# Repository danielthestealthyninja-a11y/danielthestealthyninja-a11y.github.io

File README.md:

# Electrical Engineering Portfolio

## About Me

I am an Electrical Engineering student at Brigham Young University interested in circuit design, analog electronics, and hardware development. My goal is to pursue an engineering career where I can apply my knowledge of electrical circuits, signal processing, and electronic systems to solve practical problems.

This portfolio highlights projects from EC EN 340 Circuit Design 1 and demonstrates my development in circuit analysis, simulation, design, and testing. Each project includes an explanation of the engineering problem, my contributions, the results, and the skills I developed.

## Selected Projects

### 1. Inverting Op-Amp Design

**Problem:** Develop an inverting operational amplifier and understand the relationship between input and output voltage.

**My Contribution:** Designed the circuit and applied the inverting amplifier gain equation.

**Result:** Developed a working circuit design and analyzed its expected amplification.

**What This Demonstrates:** Understanding of operational amplifier configurations, circuit analysis, and voltage gain.

### 2. Laser Tag PCB

**Problem:** Develop a transmitter and receiver for a functional laser tag gun that receives player frequencies from a great distance and removes noise.

**My Contribution:** Designed first simulation schematic for the receiver, tested physical components using oscilloscope, built the receiver and transmitter schematic on KiCad, and researched and incorporated all footprints, tracks, and measurements for the final PCB design.

**Result:** Developed a working PCB that amplifies receiving player frequencies and eliminated noise through bandpass filter.

**What This Demonstrates:** Experience with oscilloscope testing, simulation, KiCad simulation plus PCB design, and low-pass and high-pass filters.

## Design Journey

At the beginning of this semester, I was still developing my ability to take circuit concepts from equations and turn them into complete engineering designs. I have become more comfortable analyzing circuits, calculating expected behavior, and using simulation to evaluate whether a design meets its intended purpose.

One challenge I encountered was with my breadboard testing. Initially, my simulation was using unrealistic values. This led me to change my whole simulation design before I created another working one. Then when I got to testing my physical replication with the oscilloscope I realized that I needed to revise what I declared as ground and virtual ground. This setback led to much wire rearrangement and clean up, but I eventually found that I had wired something wrong which led to my ground problems. After fixing this wire I again tested my design and found through the oscilloscope that my circuit was amplifying my desired frequencies and eliminating the noise.

Through this process, I learned that designing a circuit requires more than simply calculating component values. It requires testing assumptions, identifying problems, being willing to reevaluate, and making improvements based on actual results and data.

I can now approach circuit-design problems more independently and understand how analysis, simulation, and testing work together in the engineering process.

## BYU Aims Connection

One BYU Aim that connects with my experience in EC EN 340 is **Intellectually Enlarging**.

Throughout this semester, I have learned to apply theoretical concepts to practical engineering problems. Rather than simply memorizing equations, I have developed a better understanding of how circuits behave and how to use engineering tools to design and evaluate systems.

This experience reflects BYU's goal of developing students who can think critically, develop professional competence, and apply their education to real-world problems.

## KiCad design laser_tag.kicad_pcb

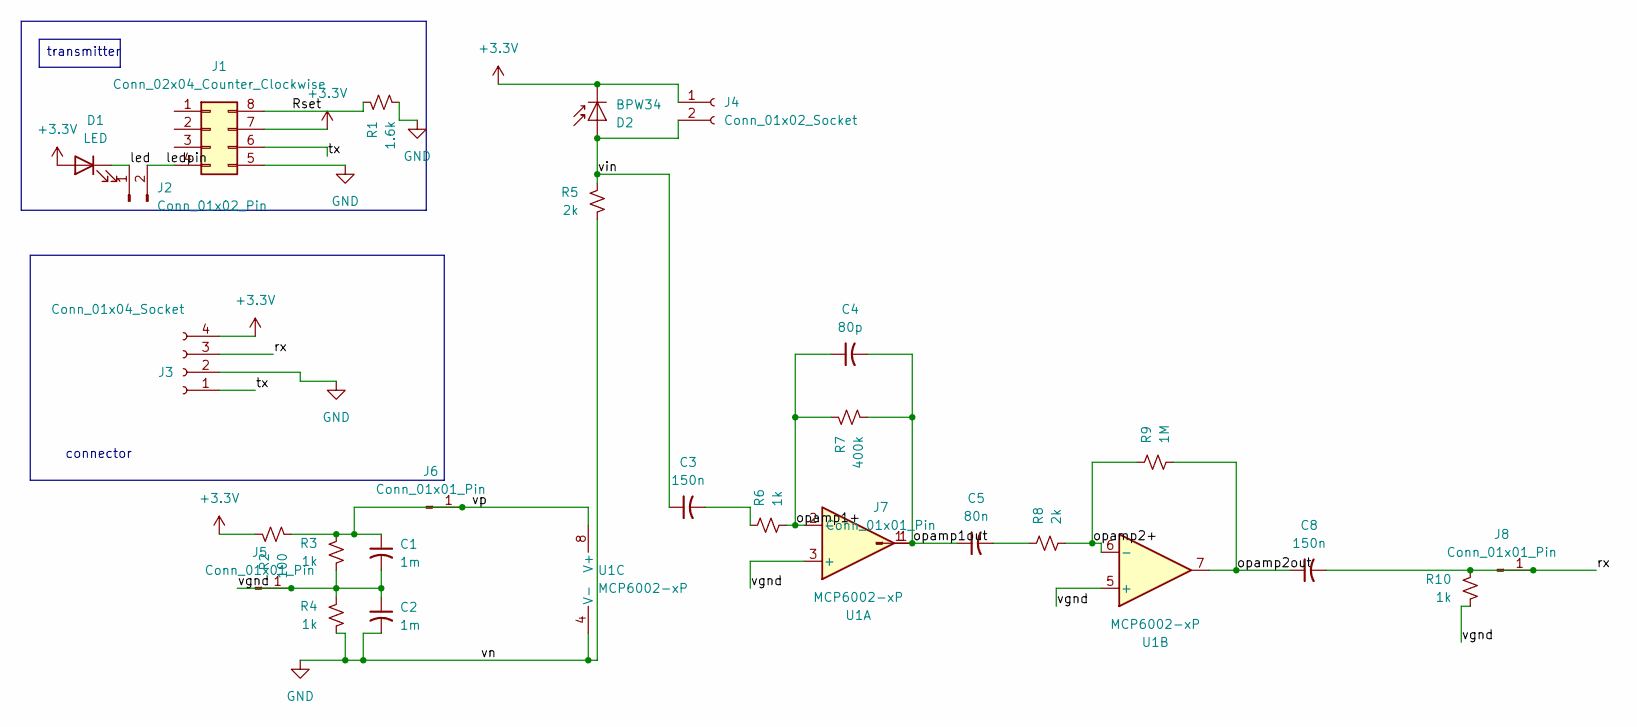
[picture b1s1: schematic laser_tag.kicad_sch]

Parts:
C1, C2: 1m; CP_Radial_D8.0mm_P3.50mm
C3, C8: 150n; C_Disc_D5.0mm_W2.5mm_P2.50mm
C4: 80p; C_Rect_L4.0mm_W2.5mm_P2.50mm
C5: 80n; C_Disc_D5.0mm_W2.5mm_P2.50mm
D1: LED; LED_D3.0mm
D2: BPW34; Osram_DIL2_4.3x4.65mm_P5.08mm
J1: Conn_02x04_Counter_Clockwise; DIP-8_W7.62mm
J2: Conn_01x02_Pin; PinHeader_1x02_P2.54mm_Vertical
J3: Conn_01x04_Socket; PinSocket_1x04_P2.54mm_Vertical
J4: Conn_01x02_Socket; JST_PH_B2B-PH-K_1x02_P2.00mm_Vertical
J5, J6, J7, J8: Conn_01x01_Pin; PinHeader_1x01_P2.54mm_Vertical
R1: 1.6k; R_Axial_DIN0207_L6.3mm_D2.5mm_P7.62mm_Horizontal
R2: 100; R_Axial_DIN0207_L6.3mm_D2.5mm_P7.62mm_Horizontal
R3, R4, R6, R10: 1k; R_Axial_DIN0207_L6.3mm_D2.5mm_P7.62mm_Horizontal
R5, R8: 2k; R_Axial_DIN0207_L6.3mm_D2.5mm_P7.62mm_Horizontal
R7: 400k; R_Axial_DIN0207_L6.3mm_D2.5mm_P7.62mm_Horizontal
R9: 1M; R_Axial_DIN0207_L6.3mm_D2.5mm_P7.62mm_Horizontal
U1: MCP6002-xP; DIP-8_W7.62mm

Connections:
+3.3V: D1.2 (A), D2.1 (K), J1.7, J3.4, J4.1, R2.1
/Rset: J1.8, R1.1
/led: D1.1 (K), J2.1
/ledpin: J1.4, J2.2
/opamp1+: C4.1, R6.2, R7.1, U1.2 (-)
/opamp1out: C4.2, C5.1, J7.1 (Pin_1_1), R7.2, U1.1
/opamp2+: R8.2, R9.1, U1.6 (-)
/opamp2out: C8.1, R9.2, U1.7
/rx: C8.2, J3.3, J8.1 (Pin_1_1), R10.1
/tx: J1.6, J3.1
/vgnd: C1.2, C2.1, J5.1 (Pin_1_1), R3.2, R4.1, R10.2, U1.3 (+), U1.5 (+)
/vin: C3.1, D2.2 (A), J4.2, R5.1
/vp: C1.1, J6.1 (Pin_1_1), R2.2, R3.1, U1.8 (V+)
GND: C2.2, J1.5, J3.2, R1.2, R4.2, R5.2, U1.4 (V-)
unnamed: C3.2, R6.1
unnamed: C5.2, R8.1

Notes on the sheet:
connector
transmitter

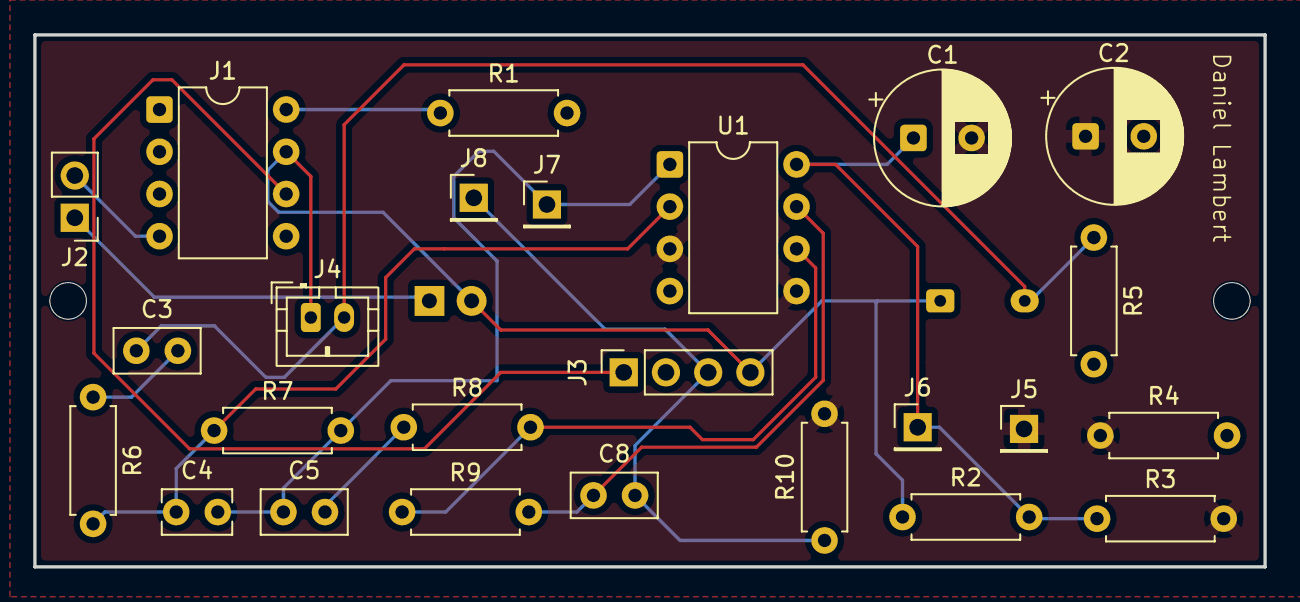
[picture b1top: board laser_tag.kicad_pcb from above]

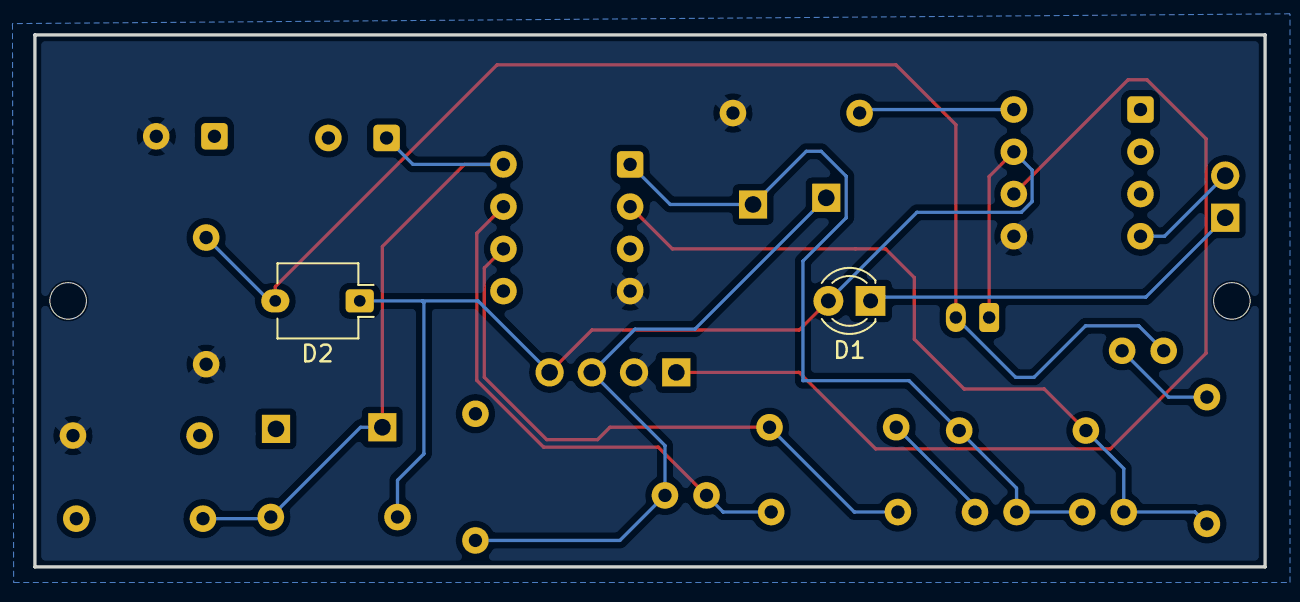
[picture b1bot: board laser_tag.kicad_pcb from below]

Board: 2 copper layers, 74.0 x 32.0 mm, 27 parts (2 on the bottom side), 16 nets.
